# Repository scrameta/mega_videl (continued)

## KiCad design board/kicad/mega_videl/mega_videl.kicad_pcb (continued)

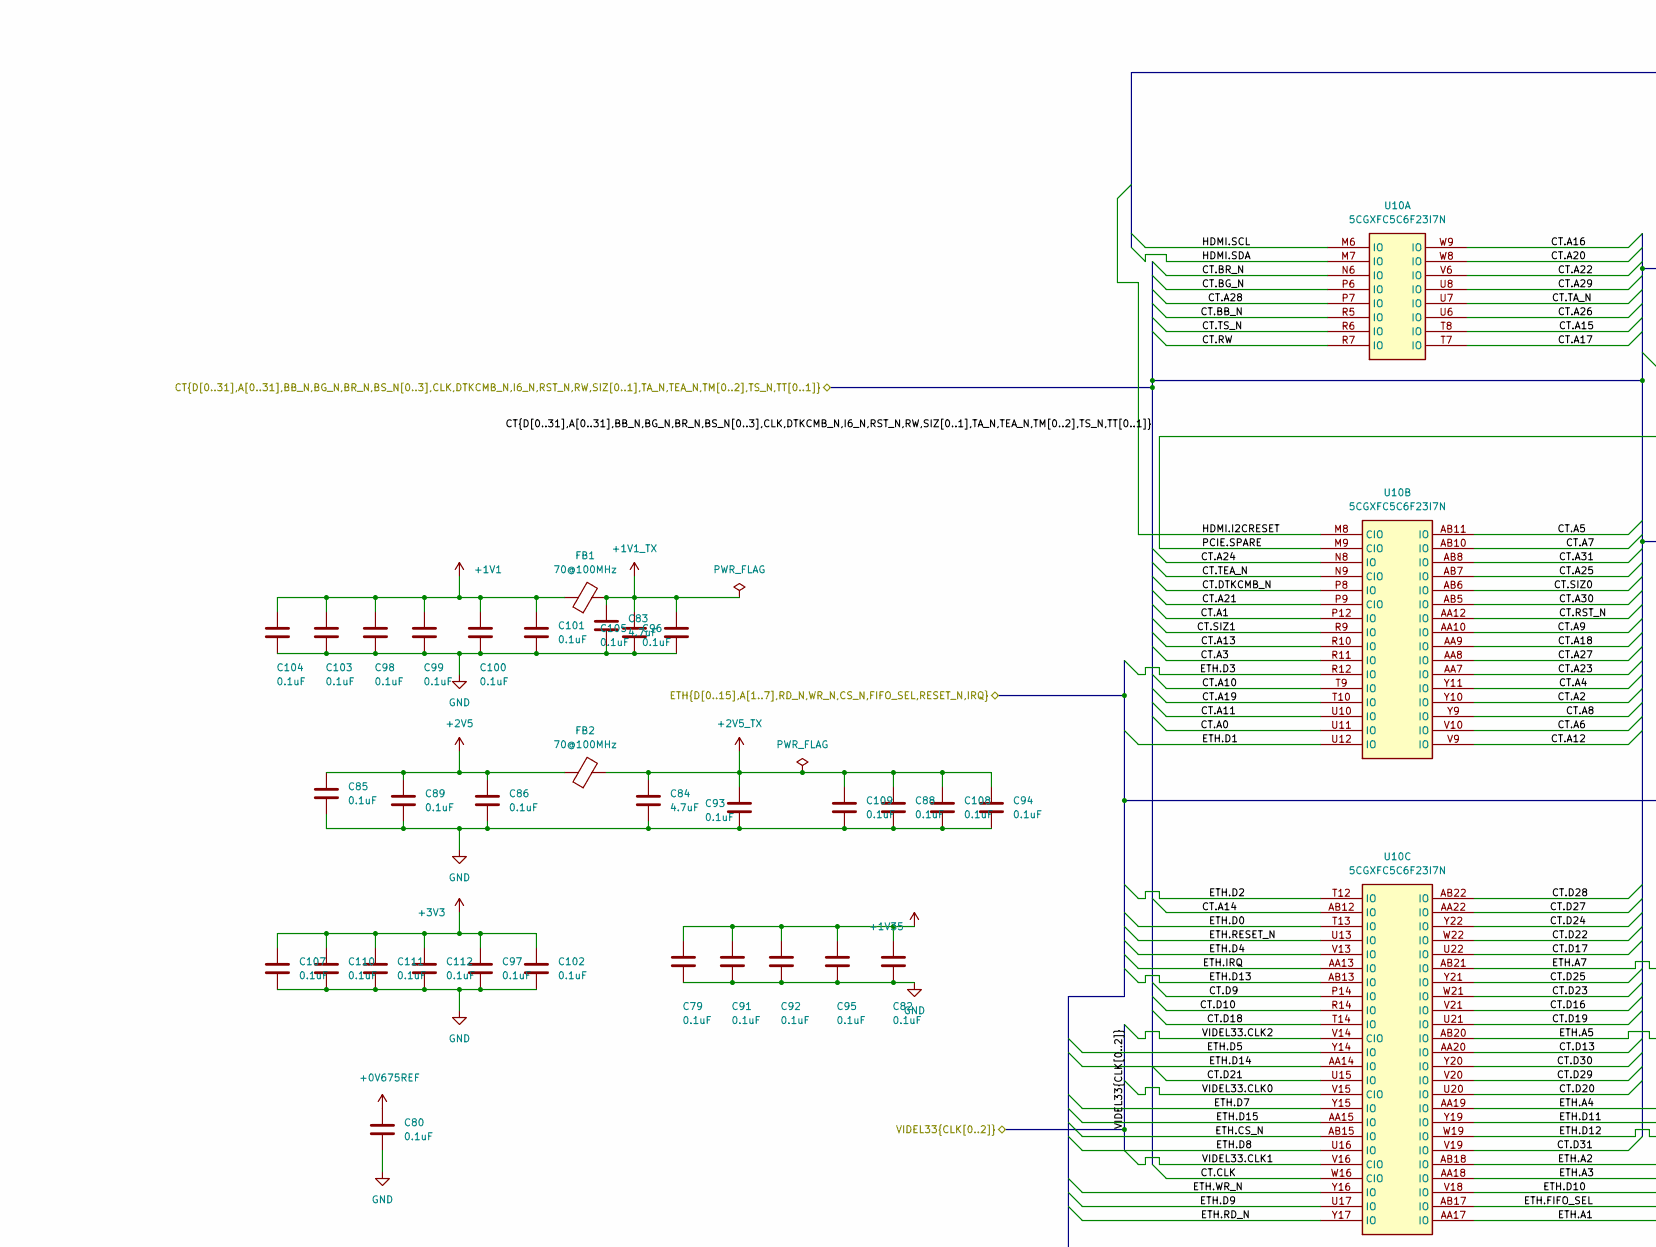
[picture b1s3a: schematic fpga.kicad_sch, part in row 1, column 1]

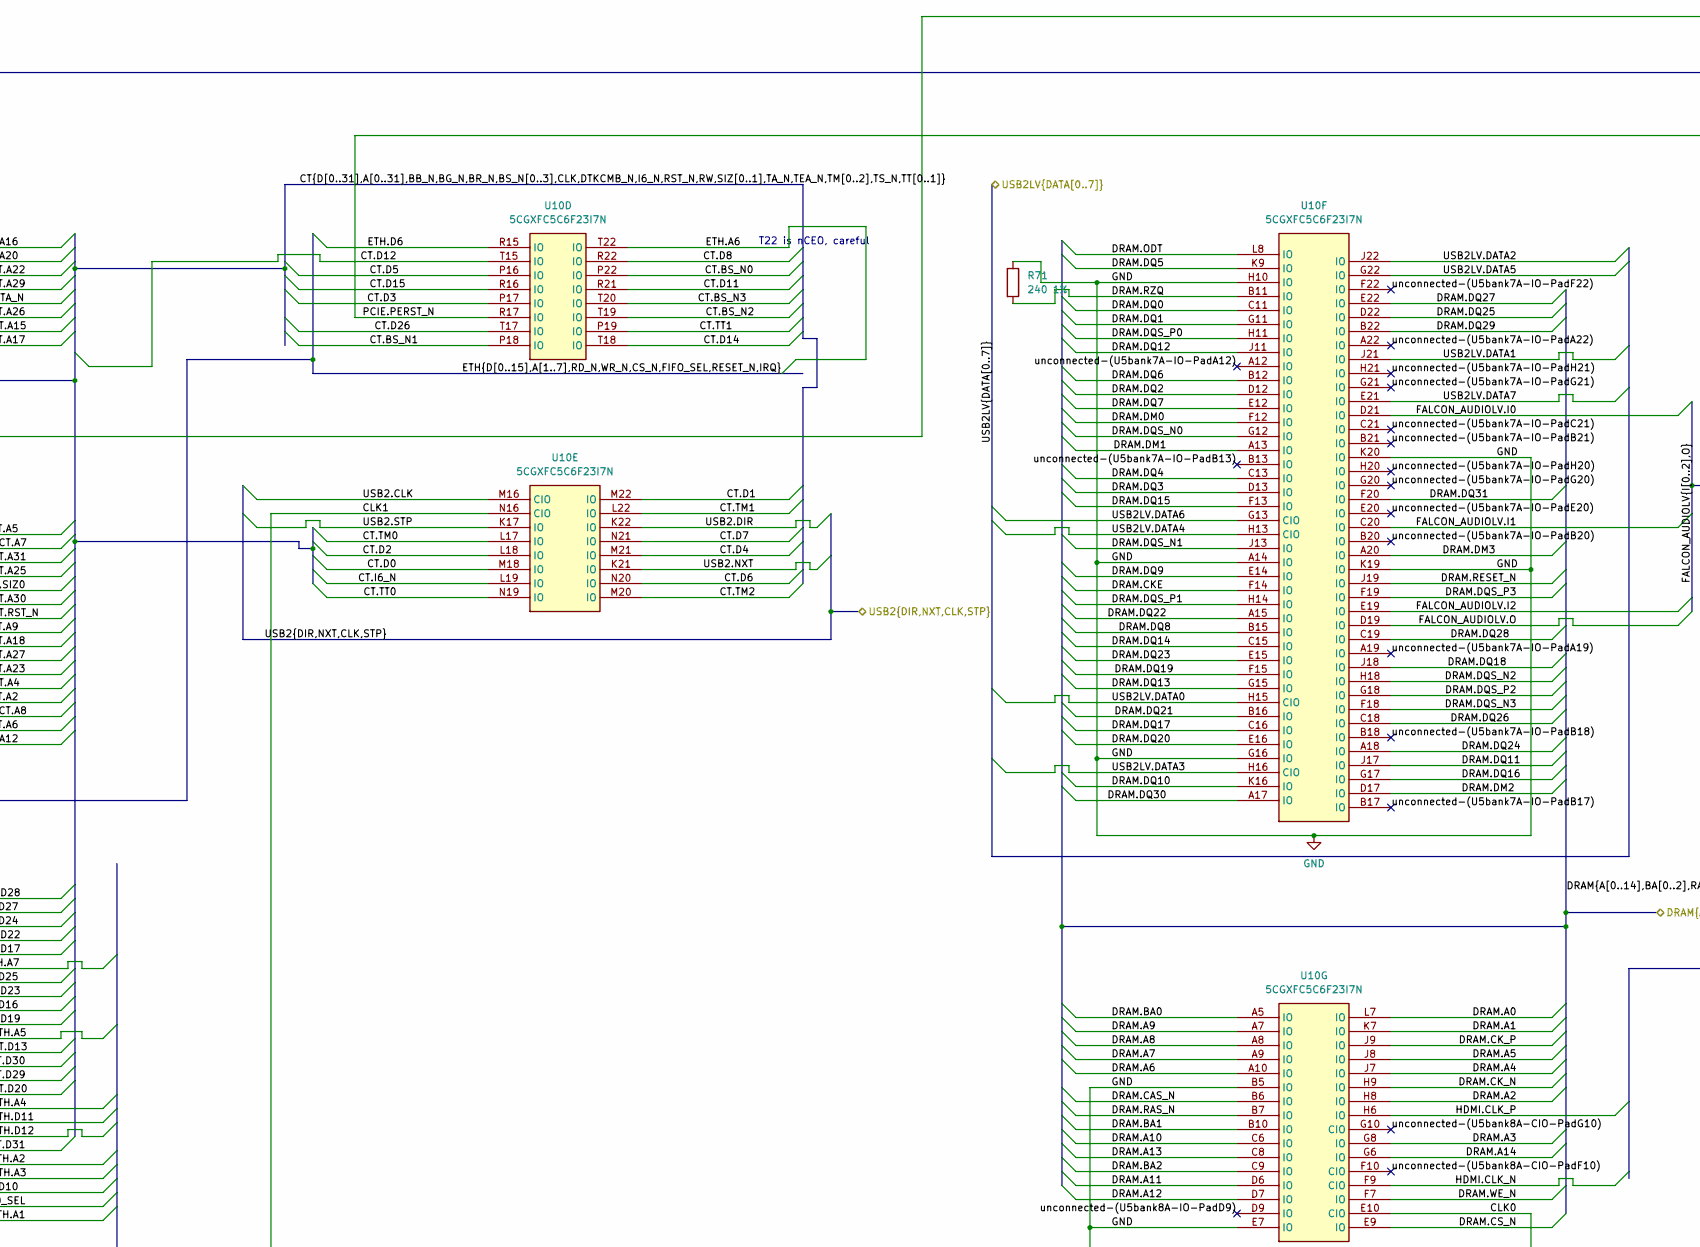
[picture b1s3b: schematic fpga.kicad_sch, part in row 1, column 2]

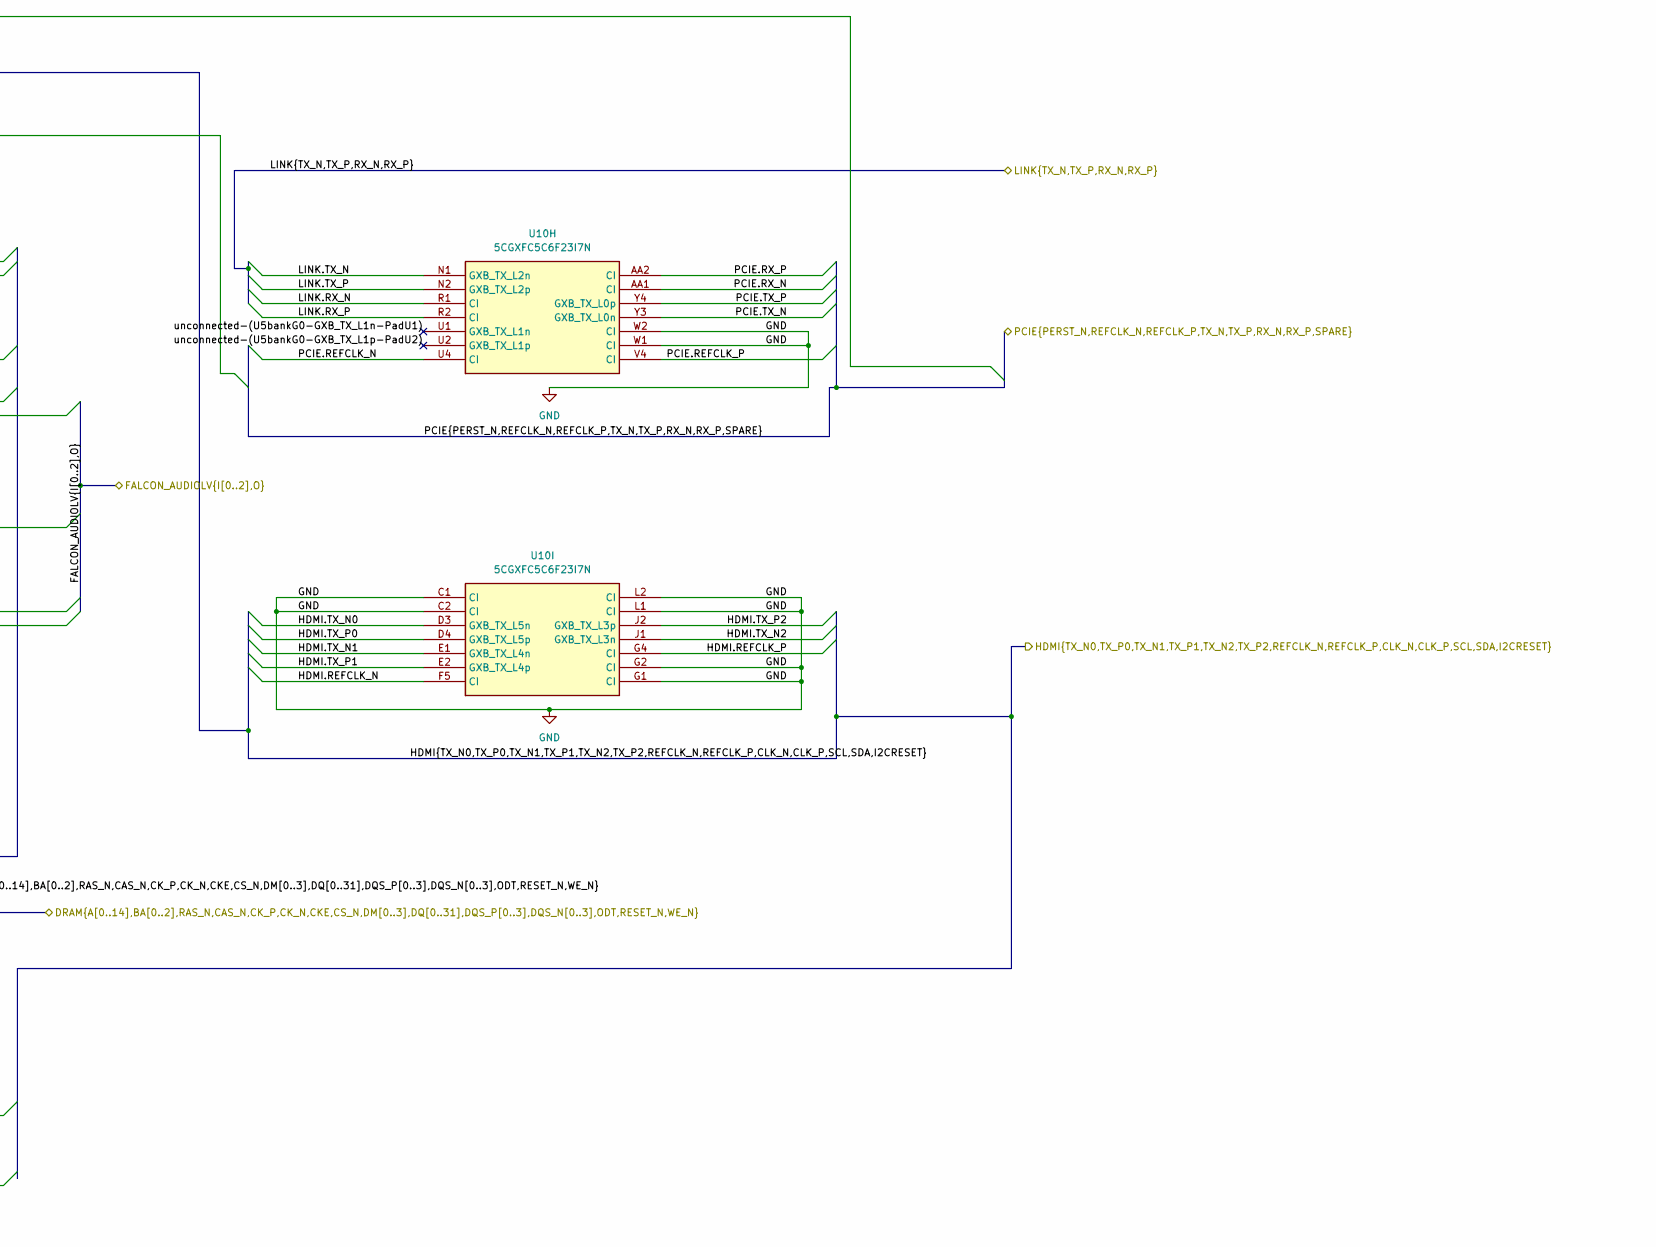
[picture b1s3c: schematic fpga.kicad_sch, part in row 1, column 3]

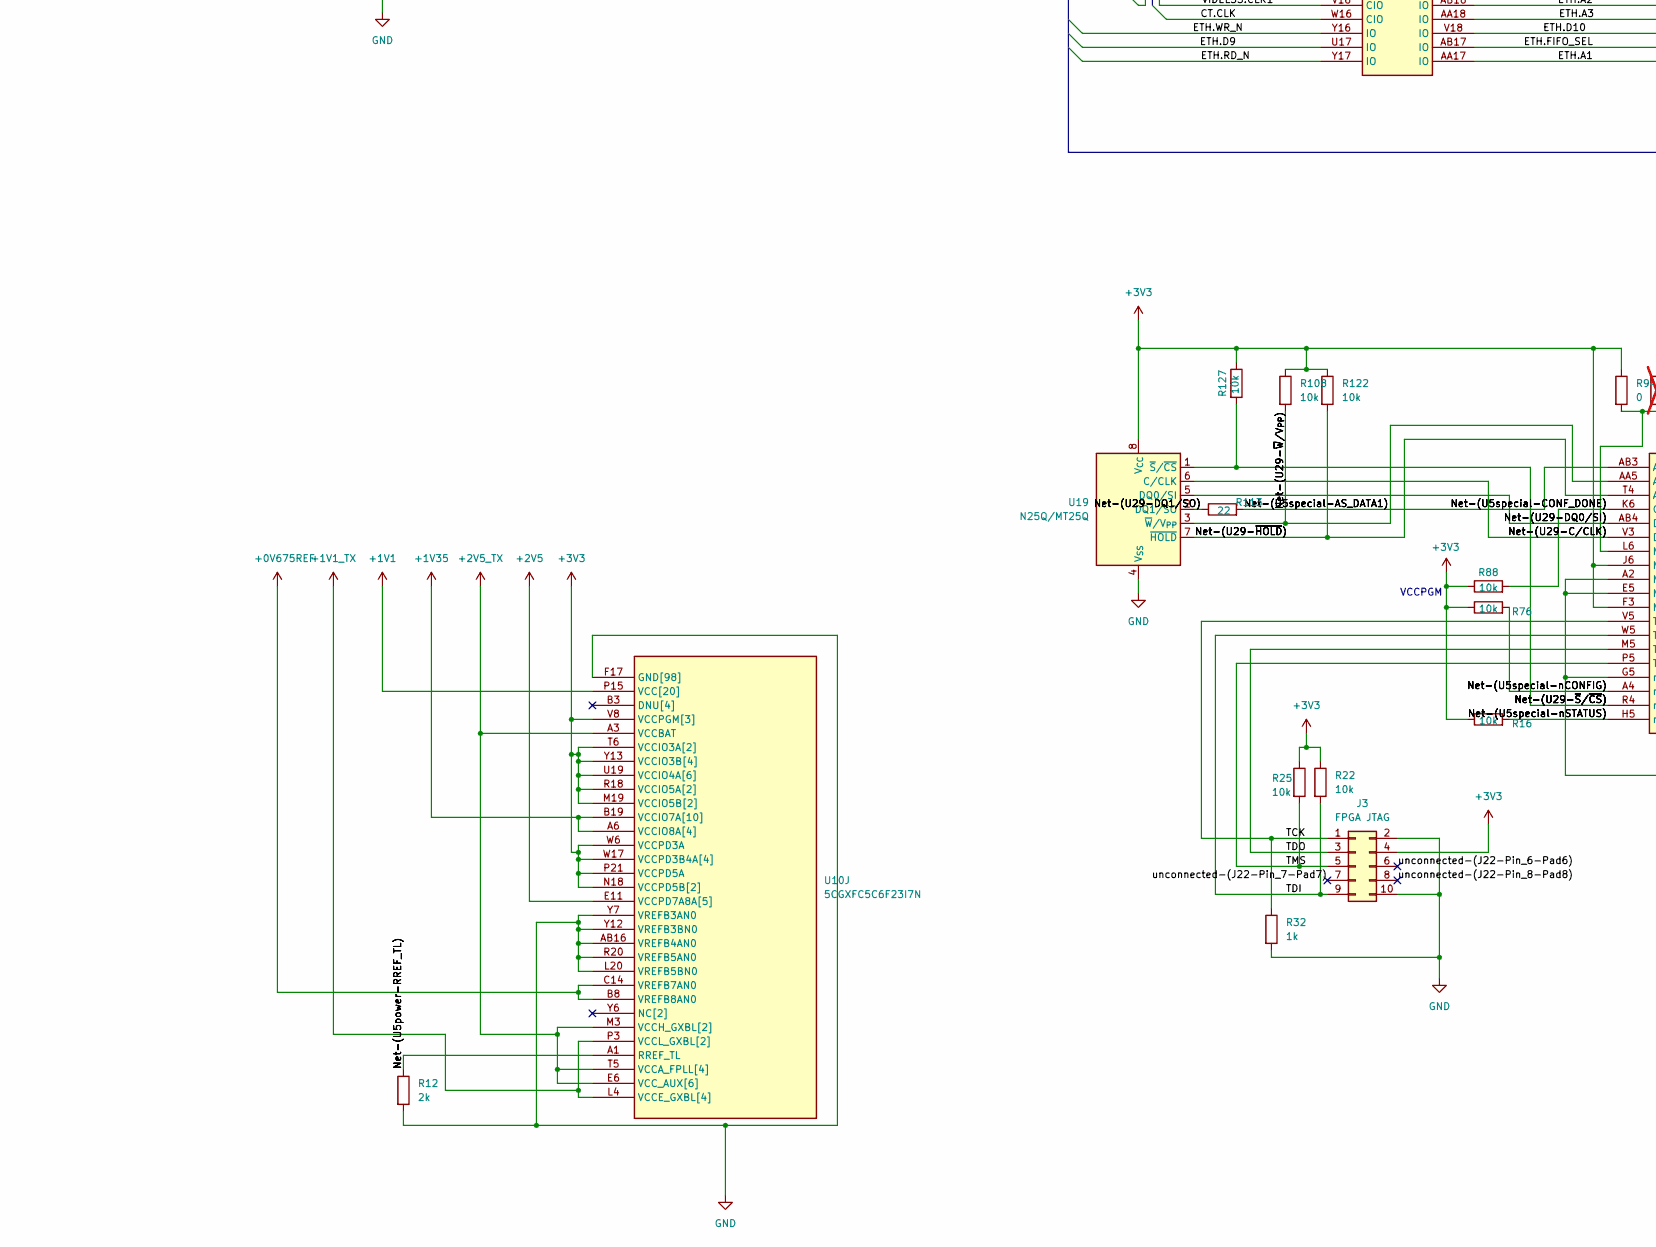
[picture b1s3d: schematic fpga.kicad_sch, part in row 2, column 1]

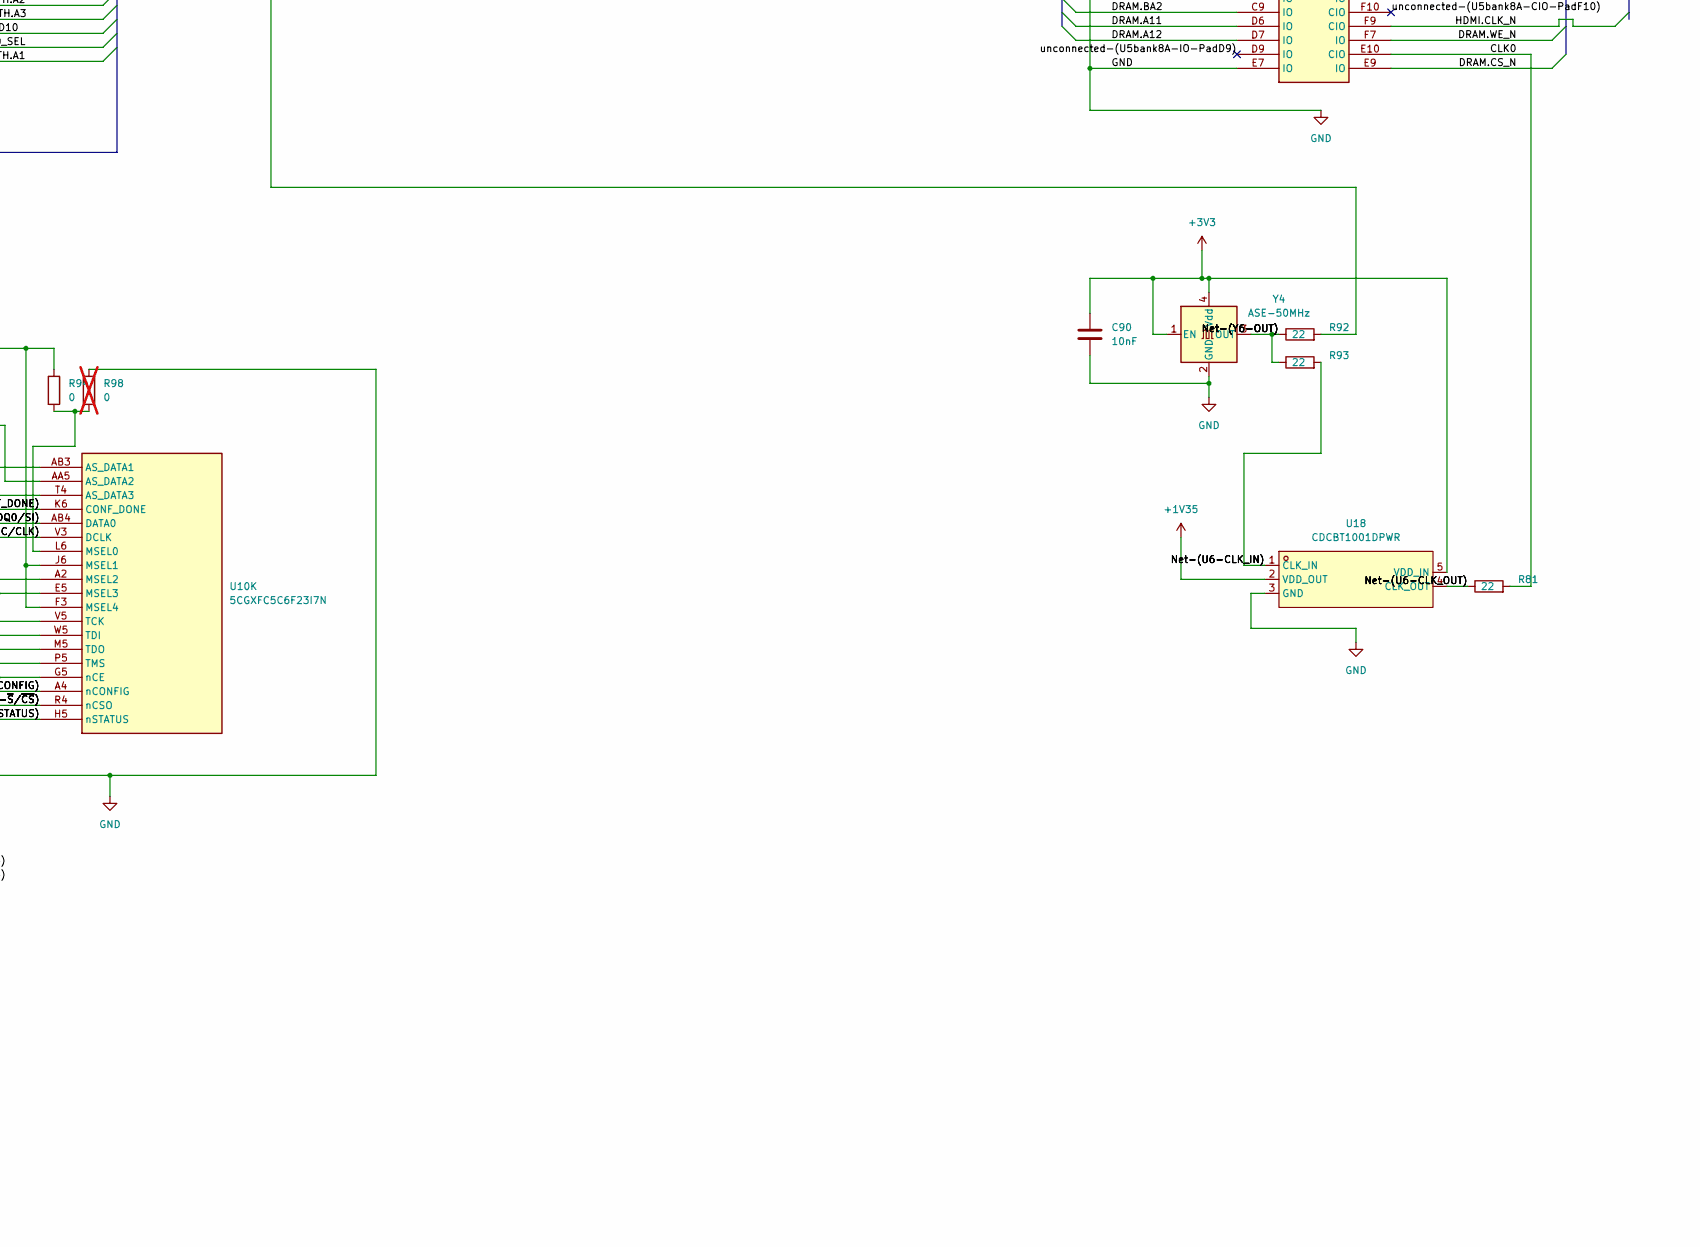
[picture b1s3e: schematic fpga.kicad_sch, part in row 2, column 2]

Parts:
C79, C80, C82, C85, C86, C88, C89, C91, C92, C93, C94, C95, C96, C97, C98, C99, C100, C101, C102, C103, C104, C105, C107, C108, C109, C110, C111, C112: 0.1uF; C_0402_1005Metric; LCSC C1525
C83, C84: 4.7uF; C_0805_2012Metric; LCSC C1779
C90: 10nF; C_0402_1005Metric; LCSC C15195
FB1, FB2: 70@100MHz; L_0805_2012Metric; LCSC C85840
J3: FPGA JTAG; IDC-Header_2x05_P2.54mm_Vertical_SMD; LCSC C17323676
R12: 2k; R_0603_1608Metric; LCSC C22975
R16, R22, R25, R76, R88, R108, R122, R127: 10k; R_0603_1608Metric; LCSC C25804
R32: 1k; R_0603_1608Metric; LCSC C21190
R71: 240 1%; R_0603_1608Metric; LCSC C23350
R81, R92, R93, R113: 22; R_0603_1608Metric; LCSC C23345
R94: 0; R_0402_1005Metric; LCSC C17168
R98: 0; R_0402_1005Metric; LCSC C17168; not fitted
U10: 5CGXFC5C6F23I7N; FBGA-484_L23.0-W23.0-R22-C22-P1.00-TL; LCSC Part C1550726
U18: CDCBT1001DPWR; X2SON-5_L0.8-W0.8-P0.48-BR; MPN CDCBT1001DPWR; LCSC Part C5215096
U19: N25Q/MT25Q; SOIC-8_5.3x6.2mm_P1.27mm; LCSC C2802705
Y4: ASE-50MHz; Oscillator_SMD_Abracon_ASE-4Pin_3.2x2.5mm; LCSC C5203552

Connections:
+0V675REF: C80.1, U10.B8 (VREFB8AN0), U10.C14 (VREFB7AN0); also elsewhere on the board
+1V1: C98.1, C99.1, C100.1, C101.1, C103.1, C104.1, FB1.1, U10.J10 (VCC[20]), U10.J12 (VCC[20]), U10.J14 (VCC[20]), U10.J16 (VCC[20]), U10.K11 (VCC[20]), U10.K13 (VCC[20]), U10.K15 (VCC[20]), U10.L10 (VCC[20]), U10.L12 (VCC[20]), U10.L14 (VCC[20]), U10.L16 (VCC[20]), U10.M11 (VCC[20]), U10.M13 (VCC[20]), U10.M15 (VCC[20]), U10.N10 (VCC[20]), U10.N12 (VCC[20]), U10.N14 (VCC[20]), U10.P11 (VCC[20]), U10.P13 (VCC[20]), U10.P15 (VCC[20]); also elsewhere on the board
+1V1_TX: C83.1, C96.1, C105.1, FB1.2, U10.J4 (VCCE_GXBL[4]), U10.K3 (VCCL_GXBL[2]), U10.K5 (VCCE_GXBL[4]), U10.L4 (VCCE_GXBL[4]), U10.N4 (VCCE_GXBL[4]), U10.P3 (VCCL_GXBL[2])
+1V35: C79.1, C82.1, C91.1, C92.1, C95.1, U10.A6 (VCCIO8A[4]), U10.A16 (VCCIO7A[10]), U10.B19 (VCCIO7A[10]), U10.C7 (VCCIO8A[4]), U10.C12 (VCCIO7A[10]), U10.C22 (VCCIO7A[10]), U10.D15 (VCCIO7A[10]), U10.E8 (VCCIO8A[4]), U10.E18 (VCCIO7A[10]), U10.F11 (VCCIO7A[10]), U10.F21 (VCCIO7A[10]), U10.G7 (VCCIO8A[4]), U10.G14 (VCCIO7A[10]), U10.H17 (VCCIO7A[10]), U18.2 (VDD_OUT); also elsewhere on the board
+2V5: C85.1, C86.1, C89.1, FB2.1, U10.C10 (VCCPD7A8A[5]), U10.D8 (VCCPD7A8A[5]), U10.D14 (VCCPD7A8A[5]), U10.D16 (VCCPD7A8A[5]), U10.E11 (VCCPD7A8A[5]); also elsewhere on the board
+2V5_TX: C84.1, C88.1, C93.1, C94.1, C108.1, C109.1, FB2.2, U10.A3 (VCCBAT), U10.D11 (VCC_AUX[6]), U10.D18 (VCC_AUX[6]), U10.E6 (VCC_AUX[6]), U10.F4 (VCCA_FPLL[4]), U10.H19 (VCCA_FPLL[4]), U10.M3 (VCCH_GXBL[2]), U10.T3 (VCCH_GXBL[2]), U10.T5 (VCCA_FPLL[4]), U10.U18 (VCCA_FPLL[4]), U10.W7 (VCC_AUX[6]), U10.W13 (VCC_AUX[6]), U10.W18 (VCC_AUX[6])
+3V3: C90.2, C97.1, C102.1, C107.1, C110.1, C111.1, C112.1, J3.4, R16.1, R22.1, R25.1, R76.1, R88.1, R94.1, R108.1, R122.1, R127.1, U10.AA16 (VCCIO4A[6]), U10.AA21 (VCCIO4A[6]), U10.F3 (MSEL4), U10.F8 (VCCPGM[3]), U10.J6 (MSEL1), U10.K18 (VCCIO5B[2]), U10.M17 (VCCPD5B[2]), U10.M19 (VCCIO5B[2]), U10.N18 (VCCPD5B[2]), U10.P20 (VCCIO5A[2]), U10.P21 (VCCPD5A), U10.R8 (VCCIO3B[4]), U10.R18 (VCCIO5A[2]), U10.R19 (VCCPGM[3]), U10.T6 (VCCIO3A[2]), U10.T11 (VCCIO3B[4]), U10.U14 (VCCIO4A[6]), U10.U19 (VCCIO4A[6]), U10.V8 (VCCPGM[3]), U10.W6 (VCCPD3A), U10.W10 (VCCIO3B[4]), U10.W11 (VCCPD3B4A[4]), U10.W12 (VCCPD3B4A[4]), U10.W14 (VCCPD3B4A[4]), U10.W15 (VCCIO4A[6]), U10.W17 (VCCPD3B4A[4]), U10.W20 (VCCIO4A[6]), U10.Y8 (VCCIO3A[2]), U10.Y13 (VCCIO3B[4]), U18.5 (VDD_IN), U19.8 (V_{CC}), Y4.1 (EN), Y4.4 (Vdd); also elsewhere on the board
/fpga/CLK0: R81.2, U10.E10 (CIO)
/fpga/CLK1: R92.2, U10.N16 (CIO)
/fpga/CT.A0: U10.U11 (IO); also elsewhere on the board
/fpga/CT.A1: U10.P12 (IO); also elsewhere on the board
/fpga/CT.A2: U10.Y10 (IO); also elsewhere on the board
/fpga/CT.A3: U10.R11 (IO); also elsewhere on the board
/fpga/CT.A4: U10.Y11 (IO); also elsewhere on the board
/fpga/CT.A5: U10.AB11 (IO); also elsewhere on the board
/fpga/CT.A6: U10.V10 (IO); also elsewhere on the board
/fpga/CT.A7: U10.AB10 (IO); also elsewhere on the board
/fpga/CT.A8: U10.Y9 (IO); also elsewhere on the board
/fpga/CT.A9: U10.AA10 (IO); also elsewhere on the board
/fpga/CT.A10: U10.T9 (IO); also elsewhere on the board
/fpga/CT.A11: U10.U10 (IO); also elsewhere on the board
/fpga/CT.A12: U10.V9 (IO); also elsewhere on the board
/fpga/CT.A13: U10.R10 (IO); also elsewhere on the board
/fpga/CT.A14: U10.AB12 (IO); also elsewhere on the board
/fpga/CT.A15: U10.T8 (IO); also elsewhere on the board
/fpga/CT.A16: U10.W9 (IO); also elsewhere on the board
/fpga/CT.A17: U10.T7 (IO); also elsewhere on the board
/fpga/CT.A18: U10.AA9 (IO); also elsewhere on the board
/fpga/CT.A19: U10.T10 (IO); also elsewhere on the board
/fpga/CT.A20: U10.W8 (IO); also elsewhere on the board
/fpga/CT.A21: U10.P9 (CIO); also elsewhere on the board
/fpga/CT.A22: U10.V6 (IO); also elsewhere on the board
/fpga/CT.A23: U10.AA7 (IO); also elsewhere on the board
/fpga/CT.A24: U10.N8 (IO); also elsewhere on the board
/fpga/CT.A25: U10.AB7 (IO); also elsewhere on the board
/fpga/CT.A26: U10.U6 (IO); also elsewhere on the board
/fpga/CT.A27: U10.AA8 (IO); also elsewhere on the board
/fpga/CT.A28: U10.P7 (IO); also elsewhere on the board
/fpga/CT.A29: U10.U8 (IO); also elsewhere on the board
/fpga/CT.A30: U10.AB5 (IO); also elsewhere on the board
/fpga/CT.A31: U10.AB8 (IO); also elsewhere on the board
/fpga/CT.BB_N: U10.R5 (IO); also elsewhere on the board
/fpga/CT.BG_N: U10.P6 (IO); also elsewhere on the board
/fpga/CT.BR_N: U10.N6 (IO); also elsewhere on the board
/fpga/CT.BS_N0: U10.P22 (IO); also elsewhere on the board
/fpga/CT.BS_N1: U10.P18 (IO); also elsewhere on the board
/fpga/CT.BS_N2: U10.T19 (IO); also elsewhere on the board
/fpga/CT.BS_N3: U10.T20 (IO); also elsewhere on the board
/fpga/CT.CLK: U10.W16 (CIO); also elsewhere on the board
/fpga/CT.D0: U10.M18 (IO); also elsewhere on the board
/fpga/CT.D1: U10.M22 (IO); also elsewhere on the board
/fpga/CT.D2: U10.L18 (IO); also elsewhere on the board
/fpga/CT.D3: U10.P17 (IO); also elsewhere on the board
/fpga/CT.D4: U10.M21 (IO); also elsewhere on the board
/fpga/CT.D5: U10.P16 (IO); also elsewhere on the board
/fpga/CT.D6: U10.N20 (IO); also elsewhere on the board
/fpga/CT.D7: U10.N21 (IO); also elsewhere on the board
/fpga/CT.D8: U10.R22 (IO); also elsewhere on the board
/fpga/CT.D9: U10.P14 (IO); also elsewhere on the board
/fpga/CT.D10: U10.R14 (IO); also elsewhere on the board
/fpga/CT.D11: U10.R21 (IO); also elsewhere on the board
/fpga/CT.D12: U10.T15 (IO); also elsewhere on the board
/fpga/CT.D13: U10.AA20 (IO); also elsewhere on the board
/fpga/CT.D14: U10.T18 (IO); also elsewhere on the board
/fpga/CT.D15: U10.R16 (IO); also elsewhere on the board
/fpga/CT.D16: U10.V21 (IO); also elsewhere on the board
/fpga/CT.D17: U10.U22 (IO); also elsewhere on the board
/fpga/CT.D18: U10.T14 (IO); also elsewhere on the board
/fpga/CT.D19: U10.U21 (IO); also elsewhere on the board
/fpga/CT.D20: U10.U20 (IO); also elsewhere on the board
/fpga/CT.D21: U10.U15 (IO); also elsewhere on the board
/fpga/CT.D22: U10.W22 (IO); also elsewhere on the board
/fpga/CT.D23: U10.W21 (IO); also elsewhere on the board
/fpga/CT.D24: U10.Y22 (IO); also elsewhere on the board
/fpga/CT.D25: U10.Y21 (IO); also elsewhere on the board
/fpga/CT.D26: U10.T17 (IO); also elsewhere on the board
/fpga/CT.D27: U10.AA22 (IO); also elsewhere on the board
/fpga/CT.D28: U10.AB22 (IO); also elsewhere on the board
/fpga/CT.D29: U10.V20 (IO); also elsewhere on the board
/fpga/CT.D30: U10.Y20 (IO); also elsewhere on the board
/fpga/CT.D31: U10.V19 (IO); also elsewhere on the board
/fpga/CT.DTKCMB_N: U10.P8 (IO); also elsewhere on the board
/fpga/CT.I6_N: U10.L19 (IO); also elsewhere on the board
/fpga/CT.RST_N: U10.AA12 (IO); also elsewhere on the board
/fpga/CT.RW: U10.R7 (IO); also elsewhere on the board
/fpga/CT.SIZ0: U10.AB6 (IO); also elsewhere on the board
/fpga/CT.SIZ1: U10.R9 (IO); also elsewhere on the board
/fpga/CT.TA_N: U10.U7 (IO); also elsewhere on the board
/fpga/CT.TEA_N: U10.N9 (CIO); also elsewhere on the board
/fpga/CT.TM0: U10.L17 (IO); also elsewhere on the board
/fpga/CT.TM1: U10.L22 (IO); also elsewhere on the board
/fpga/CT.TM2: U10.M20 (IO); also elsewhere on the board
/fpga/CT.TS_N: U10.R6 (IO); also elsewhere on the board
/fpga/CT.TT0: U10.N19 (IO); also elsewhere on the board
/fpga/CT.TT1: U10.P19 (IO); also elsewhere on the board
/fpga/DRAM.A0: U10.L7 (IO); also elsewhere on the board
/fpga/DRAM.A1: U10.K7 (IO); also elsewhere on the board
/fpga/DRAM.A2: U10.H8 (IO); also elsewhere on the board
/fpga/DRAM.A3: U10.G8 (IO); also elsewhere on the board
/fpga/DRAM.A4: U10.J7 (IO); also elsewhere on the board
/fpga/DRAM.A5: U10.J8 (IO); also elsewhere on the board
/fpga/DRAM.A6: U10.A10 (IO); also elsewhere on the board
/fpga/DRAM.A7: U10.A9 (IO); also elsewhere on the board
/fpga/DRAM.A8: U10.A8 (IO); also elsewhere on the board
/fpga/DRAM.A9: U10.A7 (IO); also elsewhere on the board
/fpga/DRAM.A10: U10.C6 (IO); also elsewhere on the board
/fpga/DRAM.A11: U10.D6 (IO); also elsewhere on the board
/fpga/DRAM.A12: U10.D7 (IO); also elsewhere on the board
/fpga/DRAM.A13: U10.C8 (IO); also elsewhere on the board
/fpga/DRAM.A14: U10.G6 (IO); also elsewhere on the board
/fpga/DRAM.BA0: U10.A5 (IO); also elsewhere on the board
/fpga/DRAM.BA1: U10.B10 (IO); also elsewhere on the board
/fpga/DRAM.BA2: U10.C9 (IO); also elsewhere on the board
/fpga/DRAM.CAS_N: U10.B6 (IO); also elsewhere on the board
/fpga/DRAM.CKE: U10.F14 (IO); also elsewhere on the board
/fpga/DRAM.CK_N: U10.H9 (IO); also elsewhere on the board
/fpga/DRAM.CK_P: U10.J9 (IO); also elsewhere on the board
/fpga/DRAM.CS_N: U10.E9 (IO); also elsewhere on the board
/fpga/DRAM.DM0: U10.F12 (IO); also elsewhere on the board
/fpga/DRAM.DM1: U10.A13 (IO); also elsewhere on the board
/fpga/DRAM.DM2: U10.D17 (IO); also elsewhere on the board
/fpga/DRAM.DM3: U10.A20 (IO); also elsewhere on the board
/fpga/DRAM.DQ0: U10.C11 (IO); also elsewhere on the board
/fpga/DRAM.DQ1: U10.G11 (IO); also elsewhere on the board
/fpga/DRAM.DQ2: U10.D12 (IO); also elsewhere on the board
/fpga/DRAM.DQ3: U10.D13 (IO); also elsewhere on the board
/fpga/DRAM.DQ4: U10.C13 (IO); also elsewhere on the board
/fpga/DRAM.DQ5: U10.K9 (IO); also elsewhere on the board
/fpga/DRAM.DQ6: U10.B12 (IO); also elsewhere on the board
/fpga/DRAM.DQ7: U10.E12 (IO); also elsewhere on the board
/fpga/DRAM.DQ8: U10.B15 (IO); also elsewhere on the board
/fpga/DRAM.DQ9: U10.E14 (IO); also elsewhere on the board
/fpga/DRAM.DQ10: U10.K16 (IO); also elsewhere on the board
/fpga/DRAM.DQ11: U10.J17 (IO); also elsewhere on the board
/fpga/DRAM.DQ12: U10.J11 (IO); also elsewhere on the board
/fpga/DRAM.DQ13: U10.G15 (IO); also elsewhere on the board
/fpga/DRAM.DQ14: U10.C15 (IO); also elsewhere on the board
/fpga/DRAM.DQ15: U10.F13 (IO); also elsewhere on the board
/fpga/DRAM.DQ16: U10.G17 (IO); also elsewhere on the board
/fpga/DRAM.DQ17: U10.C16 (IO); also elsewhere on the board
/fpga/DRAM.DQ18: U10.J18 (IO); also elsewhere on the board
/fpga/DRAM.DQ19: U10.F15 (IO); also elsewhere on the board
/fpga/DRAM.DQ20: U10.E16 (IO); also elsewhere on the board
/fpga/DRAM.DQ21: U10.B16 (IO); also elsewhere on the board
/fpga/DRAM.DQ22: U10.A15 (IO); also elsewhere on the board
/fpga/DRAM.DQ23: U10.E15 (IO); also elsewhere on the board
/fpga/DRAM.DQ24: U10.A18 (IO); also elsewhere on the board
/fpga/DRAM.DQ25: U10.D22 (IO); also elsewhere on the board
/fpga/DRAM.DQ26: U10.C18 (IO); also elsewhere on the board
/fpga/DRAM.DQ27: U10.E22 (IO); also elsewhere on the board
/fpga/DRAM.DQ28: U10.C19 (IO); also elsewhere on the board
/fpga/DRAM.DQ29: U10.B22 (IO); also elsewhere on the board
/fpga/DRAM.DQ30: U10.A17 (IO); also elsewhere on the board
/fpga/DRAM.DQ31: U10.F20 (IO); also elsewhere on the board
/fpga/DRAM.DQS_N0: U10.G12 (IO); also elsewhere on the board
/fpga/DRAM.DQS_N1: U10.J13 (IO); also elsewhere on the board
/fpga/DRAM.DQS_N2: U10.H18 (IO); also elsewhere on the board
/fpga/DRAM.DQS_N3: U10.F18 (IO); also elsewhere on the board
/fpga/DRAM.DQS_P0: U10.H11 (IO); also elsewhere on the board
/fpga/DRAM.DQS_P1: U10.H14 (IO); also elsewhere on the board
/fpga/DRAM.DQS_P2: U10.G18 (IO); also elsewhere on the board
/fpga/DRAM.DQS_P3: U10.F19 (IO); also elsewhere on the board
/fpga/DRAM.ODT: U10.L8 (IO); also elsewhere on the board
/fpga/DRAM.RAS_N: U10.B7 (IO); also elsewhere on the board
/fpga/DRAM.RESET_N: U10.J19 (IO); also elsewhere on the board
/fpga/DRAM.RZQ: R71.2, U10.B11 (IO)
/fpga/DRAM.WE_N: U10.F7 (IO); also elsewhere on the board
/fpga/ETH.A1: U10.AA17 (IO); also elsewhere on the board
/fpga/ETH.A2: U10.AB18 (IO); also elsewhere on the board
/fpga/ETH.A3: U10.AA18 (IO); also elsewhere on the board
/fpga/ETH.A4: U10.AA19 (IO); also elsewhere on the board
/fpga/ETH.A5: U10.AB20 (IO); also elsewhere on the board
/fpga/ETH.A6: U10.T22 (IO); also elsewhere on the board
/fpga/ETH.A7: U10.AB21 (IO); also elsewhere on the board
/fpga/ETH.CS_N: U10.AB15 (IO); also elsewhere on the board
/fpga/ETH.D0: U10.T13 (IO); also elsewhere on the board
/fpga/ETH.D1: U10.U12 (IO); also elsewhere on the board
/fpga/ETH.D2: U10.T12 (IO); also elsewhere on the board
/fpga/ETH.D3: U10.R12 (IO); also elsewhere on the board
/fpga/ETH.D4: U10.V13 (IO); also elsewhere on the board
/fpga/ETH.D5: U10.Y14 (IO); also elsewhere on the board
/fpga/ETH.D6: U10.R15 (IO); also elsewhere on the board
/fpga/ETH.D7: U10.Y15 (IO); also elsewhere on the board
/fpga/ETH.D8: U10.U16 (IO); also elsewhere on the board
/fpga/ETH.D9: U10.U17 (IO); also elsewhere on the board
/fpga/ETH.D10: U10.V18 (IO); also elsewhere on the board
/fpga/ETH.D11: U10.Y19 (IO); also elsewhere on the board
/fpga/ETH.D12: U10.W19 (IO); also elsewhere on the board
/fpga/ETH.D13: U10.AB13 (IO); also elsewhere on the board
/fpga/ETH.D14: U10.AA14 (IO); also elsewhere on the board
/fpga/ETH.D15: U10.AA15 (IO); also elsewhere on the board
/fpga/ETH.FIFO_SEL: U10.AB17 (IO); also elsewhere on the board
/fpga/ETH.IRQ: U10.AA13 (IO); also elsewhere on the board
/fpga/ETH.RD_N: U10.Y17 (IO); also elsewhere on the board
/fpga/ETH.RESET_N: U10.U13 (IO); also elsewhere on the board
/fpga/ETH.WR_N: U10.Y16 (IO); also elsewhere on the board
/fpga/FALCON_AUDIOLV.I0: U10.D21 (IO); also elsewhere on the board
/fpga/FALCON_AUDIOLV.I1: U10.C20 (IO); also elsewhere on the board
/fpga/FALCON_AUDIOLV.I2: U10.E19 (IO); also elsewhere on the board
/fpga/FALCON_AUDIOLV.O: U10.D19 (IO); also elsewhere on the board
/fpga/HDMI.CLK_N: U10.F9 (CIO); also elsewhere on the board
/fpga/HDMI.CLK_P: U10.H6 (IO); also elsewhere on the board
/fpga/HDMI.I2CRESET: U10.M8 (CIO); also elsewhere on the board
/fpga/HDMI.REFCLK_N: U10.F5 (CI); also elsewhere on the board
/fpga/HDMI.REFCLK_P: U10.G4 (CI); also elsewhere on the board
/fpga/HDMI.SCL: U10.M6 (IO); also elsewhere on the board
/fpga/HDMI.SDA: U10.M7 (IO); also elsewhere on the board
/fpga/HDMI.TX_N0: U10.D3 (GXB_TX_L5n); also elsewhere on the board
/fpga/HDMI.TX_N1: U10.E1 (GXB_TX_L4n); also elsewhere on the board
/fpga/HDMI.TX_N2: U10.J1 (GXB_TX_L3n); also elsewhere on the board
/fpga/HDMI.TX_P0: U10.D4 (GXB_TX_L5p); also elsewhere on the board
/fpga/HDMI.TX_P1: U10.E2 (GXB_TX_L4p); also elsewhere on the board
/fpga/HDMI.TX_P2: U10.J2 (GXB_TX_L3p); also elsewhere on the board
/fpga/LINK.RX_N: U10.R1 (CI); also elsewhere on the board
/fpga/LINK.RX_P: U10.R2 (CI); also elsewhere on the board
/fpga/LINK.TX_N: U10.N1 (GXB_TX_L2n); also elsewhere on the board
/fpga/LINK.TX_P: U10.N2 (GXB_TX_L2p); also elsewhere on the board
/fpga/Net-(U5power-RREF_TL): R12.1, U10.A1 (RREF_TL)
/fpga/Net-(U5special-AS_DATA1): R113.2, U10.AB3 (AS_DATA1)
/fpga/Net-(U5special-CONF_DONE): R88.2, U10.K6 (CONF_DONE)
/fpga/Net-(U5special-nCONFIG): R76.2, U10.A4 (nCONFIG)
/fpga/Net-(U5special-nSTATUS): R16.2, U10.H5 (nSTATUS)
/fpga/Net-(U6-CLK_IN): R93.2, U18.1 (CLK_IN)
/fpga/Net-(U6-CLK_OUT): R81.1, U18.4 (CLK_OUT)
/fpga/Net-(U29-C/CLK): U10.V3 (DCLK), U19.6 (C/CLK)
/fpga/Net-(U29-DQ0/SI): U10.AB4 (DATA0), U19.5 (DQ0/SI)
/fpga/Net-(U29-DQ1/SO): R113.1, U19.2 (DQ1/SO)
/fpga/Net-(U29-~HOLD): R122.2, U10.T4 (AS_DATA3), U19.7 (~HOLD)
/fpga/Net-(U29-~S/~CS): R127.2, U10.R4 (nCSO), U19.1 (~S/~CS)
/fpga/Net-(U29-~W/V_{PP}): R108.2, U10.AA5 (AS_DATA2), U19.3 (~W/V_{PP})
/fpga/Net-(Y6-OUT): R92.1, R93.1, Y4.3 (OUT)
/fpga/PCIE.PERST_N: U10.R17 (IO); also elsewhere on the board
/fpga/PCIE.REFCLK_N: U10.U4 (CI); also elsewhere on the board
/fpga/PCIE.REFCLK_P: U10.V4 (CI); also elsewhere on the board
/fpga/PCIE.RX_N: U10.AA1 (CI); also elsewhere on the board
/fpga/PCIE.RX_P: U10.AA2 (CI); also elsewhere on the board
/fpga/PCIE.SPARE: U10.M9 (CIO); also elsewhere on the board
/fpga/PCIE.TX_N: U10.Y3 (GXB_TX_L0n); also elsewhere on the board
/fpga/PCIE.TX_P: U10.Y4 (GXB_TX_L0p); also elsewhere on the board
/fpga/TCK: J3.1, R32.1, U10.V5 (TCK)
/fpga/TDI: J3.9, R22.2, U10.W5 (TDI)
/fpga/TDO: J3.3, U10.M5 (TDO)
/fpga/TMS: J3.5, R25.2, U10.P5 (TMS)
/fpga/USB2.CLK: U10.M16 (CIO); also elsewhere on the board
/fpga/USB2.DIR: U10.K22 (IO); also elsewhere on the board
/fpga/USB2.NXT: U10.K21 (IO); also elsewhere on the board
/fpga/USB2.STP: U10.K17 (IO); also elsewhere on the board
/fpga/USB2LV.DATA0: U10.H15 (CIO); also elsewhere on the board
/fpga/USB2LV.DATA1: U10.J21 (IO); also elsewhere on the board
/fpga/USB2LV.DATA2: U10.J22 (IO); also elsewhere on the board
/fpga/USB2LV.DATA3: U10.H16 (CIO); also elsewhere on the board
/fpga/USB2LV.DATA4: U10.H13 (CIO); also elsewhere on the board
/fpga/USB2LV.DATA5: U10.G22 (IO); also elsewhere on the board
/fpga/USB2LV.DATA6: U10.G13 (CIO); also elsewhere on the board
/fpga/USB2LV.DATA7: U10.E21 (IO); also elsewhere on the board
/fpga/VIDEL33.CLK0: U10.V15 (CIO); also elsewhere on the board
/fpga/VIDEL33.CLK1: U10.V16 (CIO); also elsewhere on the board
/fpga/VIDEL33.CLK2: U10.V14 (CIO); also elsewhere on the board
/fpga/unconnected-(J22-Pin_6-Pad6): J3.6
/fpga/unconnected-(J22-Pin_7-Pad7): J3.7
/fpga/unconnected-(J22-Pin_8-Pad8): J3.8
/fpga/unconnected-(U5bank7A-IO-PadA12): U10.A12 (IO)
/fpga/unconnected-(U5bank7A-IO-PadA19): U10.A19 (IO)
/fpga/unconnected-(U5bank7A-IO-PadA22): U10.A22 (IO)
/fpga/unconnected-(U5bank7A-IO-PadB13): U10.B13 (IO)
/fpga/unconnected-(U5bank7A-IO-PadB17): U10.B17 (IO)
/fpga/unconnected-(U5bank7A-IO-PadB18): U10.B18 (IO)
/fpga/unconnected-(U5bank7A-IO-PadB20): U10.B20 (IO)
/fpga/unconnected-(U5bank7A-IO-PadB21): U10.B21 (IO)
/fpga/unconnected-(U5bank7A-IO-PadC21): U10.C21 (IO)
/fpga/unconnected-(U5bank7A-IO-PadE20): U10.E20 (IO)
/fpga/unconnected-(U5bank7A-IO-PadF22): U10.F22 (IO)
/fpga/unconnected-(U5bank7A-IO-PadG20): U10.G20 (IO)
/fpga/unconnected-(U5bank7A-IO-PadG21): U10.G21 (IO)
/fpga/unconnected-(U5bank7A-IO-PadH20): U10.H20 (IO)
/fpga/unconnected-(U5bank7A-IO-PadH21): U10.H21 (IO)
/fpga/unconnected-(U5bank8A-CIO-PadF10): U10.F10 (CIO)
/fpga/unconnected-(U5bank8A-CIO-PadG10): U10.G10 (CIO)
/fpga/unconnected-(U5bank8A-IO-PadD9): U10.D9 (IO)
/fpga/unconnected-(U5bankG0-GXB_TX_L1n-PadU1): U10.U1 (GXB_TX_L1n)
/fpga/unconnected-(U5bankG0-GXB_TX_L1p-PadU2): U10.U2 (GXB_TX_L1p)
GND: C79.2, C80.2, C82.2, C83.2, C84.2, C85.2, C86.2, C88.2, C89.2, C90.1, C91.2, C92.2, C93.2, C94.2, C95.2, C96.2, C97.2, C98.2, C99.2, C100.2, C101.2, C102.2, C103.2, C104.2, C105.2, C107.2, C108.2, C109.2, C110.2, C111.2, C112.2, J3.2, J3.10, R12.2, R32.2, R71.1, R98.1, U10.A2 (MSEL2), U10.A11 (GND[98]), U10.A14 (IO), U10.A21 (GND[98]), U10.AA3 (GND[98]), U10.AA4 (GND[98]), U10.AA6 (GND[98]), U10.AA11 (GND[98]), U10.AB1 (GND[98]), U10.AB2 (GND[98]), U10.AB9 (GND[98]), U10.AB14 (GND[98]), U10.AB16 (VREFB4AN0), U10.AB19 (GND[98]), U10.B1 (GND[98]), U10.B2 (GND[98]), U10.B5 (IO), U10.B9 (GND[98]), U10.B14 (GND[98]), U10.C1 (CI), U10.C2 (CI), U10.C3 (GND[98]), U10.C4 (GND[98]), U10.C5 (GND[98]), U10.C17 (GND[98]), U10.D1 (GND[98]), U10.D2 (GND[98]), U10.D5 (GND[98]), U10.D10 (GND[98]), U10.D20 (GND[98]), U10.E3 (GND[98]), U10.E4 (GND[98]), U10.E5 (MSEL3), U10.E7 (IO), U10.E13 (GND[98]), U10.F1 (GND[98]), U10.F2 (GND[98]), U10.F6 (GND[98]), U10.F16 (GND[98]), U10.F17 (GND[98]), U10.G1 (CI), U10.G2 (CI), U10.G3 (GND[98]), U10.G5 (nCE), U10.G9 (GND[98]), U10.G16 (IO), U10.G19 (GND[98]), U10.H1 (GND[98]), U10.H2 (GND[98]), U10.H3 (GND[98]), U10.H4 (GND[98]), U10.H7 (GND[98]), U10.H10 (IO), U10.H12 (GND[98]), U10.H22 (GND[98]), U10.J3 (GND[98]), U10.J5 (GND[98]), U10.J15 (GND[98]), U10.J20 (GND[98]), U10.K1 (GND[98]), U10.K2 (GND[98]), U10.K4 (GND[98]), U10.K8 (GND[98]), U10.K10 (GND[98]), U10.K12 (GND[98]), U10.K14 (GND[98]), U10.K19 (IO), U10.K20 (IO), U10.L1 (CI), U10.L2 (CI), U10.L3 (GND[98]), U10.L5 (GND[98]), U10.L11 (GND[98]), U10.L13 (GND[98]), U10.L15 (GND[98]), U10.L20 (VREFB5BN0), U10.L21 (GND[98]), U10.M1 (GND[98]), U10.M2 (GND[98]), U10.M4 (GND[98]), U10.M10 (GND[98]), U10.M12 (GND[98]), U10.M14 (GND[98]), U10.N3 (GND[98]), U10.N5 (GND[98]), U10.N7 (GND[98]), U10.N11 (GND[98]), U10.N13 (GND[98]), U10.N15 (GND[98]), U10.N17 (GND[98]), U10.N22 (GND[98]), U10.P1 (GND[98]), U10.P2 (GND[98]), U10.P4 (GND[98]), U10.P10 (GND[98]), U10.R3 (GND[98]), U10.R13 (GND[98]), U10.R20 (VREFB5AN0), U10.T1 (GND[98]), U10.T2 (GND[98]), U10.T16 (GND[98]), U10.T21 (GND[98]), U10.U3 (GND[98]), U10.U5 (GND[98]), U10.U9 (GND[98]), U10.V1 (GND[98]), U10.V2 (GND[98]), U10.V7 (GND[98]), U10.V12 (GND[98]), U10.V17 (GND[98]), U10.V22 (GND[98]), U10.W1 (CI), U10.W2 (CI), U10.W3 (GND[98]), U10.W4 (GND[98]), U10.Y1 (GND[98]), U10.Y2 (GND[98]), U10.Y5 (GND[98]), U10.Y7 (VREFB3AN0), U10.Y12 (VREFB3BN0), U10.Y18 (GND[98]), U18.3 (GND), U19.4 (V_{SS}), Y4.2 (GND); also elsewhere on the board
unnamed: R94.2, R98.2, U10.L6 (MSEL0)

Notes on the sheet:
VCCPGM
T22 is nCEO, careful
